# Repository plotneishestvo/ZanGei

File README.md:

# ZanGei — 8HP analog BBD delay

ZanGei is a compact DIY Eurorack bucket-brigade delay, inspired by the [Erica Synths EDU BBD project](https://www.ericasynths.lv/shop/diy-kits-1/edu-diy-bbd/). Two stacked PCBs make room for two different delay chips, shared clocking and a feedback path with its own character. The goal is **character over fidelity**.

The name is a poetic nod to **残心 (*zanshin*)** in iaido and other martial arts: awareness that remains after an action. It carries that idea into sound as **残韻**—“lingering resonance,” like a bell still ringing after the strike, or an echo carrying something of the past. **ZanGei** is a coined project name, not a standard Japanese reading of those kanji.

**Prototype, not a finished kit:** the complete module has not yet been assembled, calibrated or hardware-qualified. Delay/flanger/chorus behaviour is the design intent, not a measured performance specification.

## What it does

- Mono analog audio path using **V3208D (2048 stages)** and **V3205SD (4096 stages)**.
- Parallel/series input routing for the second BBD, with a blend between the two delay branches.
- Shared CD4046 clock with TC4428AEPA driver, TIME CV and INHIBIT CV.
- Feedback CHARACTER combines pre-filtering and drive; AMOUNT controls the return level.
- Independent dry tap, final DRY/WET blend and SOFT/OFF/DARK wet-output filtering.
- **8HP / 3U**, with two **37.5 × 110 mm** PCBs; requires **±12 V and bus +5 V** through a 16-pin cable.

## Signal path

```mermaid
flowchart LR
    IN["Audio input buffer"] --> DRY["Fixed dry tap"]
    IN --> INPUT["INPUT level"]
    INPUT --> SUM["Input and feedback summer"]
    SUM --> B1["V3208D and reconstruction"]
    SUM --> ROUTE["Parallel / series source"]
    B1 --> ROUTE
    ROUTE --> B2["V3205SD and reconstruction"]
    B1 --> BLEND["Tap blend"]
    B2 --> BLEND
    BLEND --> SH["Shared sample-and-hold"]
    SH --> WET["Wet recovery and output filter"]
    WET --> MIX["DRY/WET and output buffer"]
    DRY --> MIX
    MIX --> OUT["Audio output"]
    SH --> CHAR["CHARACTER filter and drive"]
    CHAR --> AMOUNT["AMOUNT and return amplifier"]
    AMOUNT --> SUM
```

## Open and explore

Open **[`schematics/BBD_Buffer.kicad_pro`](schematics/BBD_Buffer.kicad_pro)** in **KiCad 10**. Its root schematic links seven electrical sheets; the PCB contains CORE and CONTROL side by side for editing, not one wide finished board. Project-local symbols, footprints and component models are included; KiCad's standard libraries are also required.

- [Architecture and controls](docs/ARCHITECTURE.md)
- [Prototype build, power, stack and fabrication notes](docs/BUILD.md)
- [One-module BOM](bom/v0.1/BOM.md), [grouped CSV](bom/v0.1/BOM_GROUPED.csv) and [per-reference CSV](bom/v0.1/BOM_PER_REFERENCE.csv)
- [Assembly access and sequencing](schematics/assembly/README.md) and [routing limitations](schematics/routing/README.md)
- [Panel source and printable fit prototype](mechanical/README.md)
- [Component datasheets](docs/datasheets/README.md)

The native KiCad files define the implemented circuit. Documentation and 3D envelopes do not certify physical fit or safe operation. Existing assembly/silkscreen findings, clock timing, power bring-up and complete-module performance remain prototype checks. Do not connect an unverified assembly directly to a valuable rack.

## Repository

| Directory       | Purpose                                                                  |
| --------------- | ------------------------------------------------------------------------ |
| `schematics/`   | Main KiCad design, custom libraries, component models and review records |
| `docs/`         | Self-contained architecture, build notes and datasheets                  |
| `bom/v0.1/`     | One-module parts and additional assembly hardware                        |
| `mechanical/`   | Editable panel source and panel exports                                  |
| `simulation/`   | Retained circuit studies; not complete-module validation                 |
| `test_signals/` | Audio used for listening experiments                                     |

The BOM covers 157 schematic positions plus separate sockets and hardware. Generated manufacturing files and full-board FreeCAD review assemblies are local working artifacts, not a fabrication release. See the [simulation guide](simulation/README.md) for the historical scope and requirements of the retained studies.

### PCB render:

## Licence and attribution

Project-authored schematics, PCB layouts, mechanical designs, scripts and documentation are [MIT-licensed](LICENSE), including permission to manufacture and sell hardware from the project-authored designs. See [licensing scope and third-party exceptions](docs/LICENSING.md). Third-party datasheets, library assets and simulation models retain their own notices and terms. This is an independent, AI-assisted DIY project, not an official Erica Synths, Coolaudio or other manufacturer's product.

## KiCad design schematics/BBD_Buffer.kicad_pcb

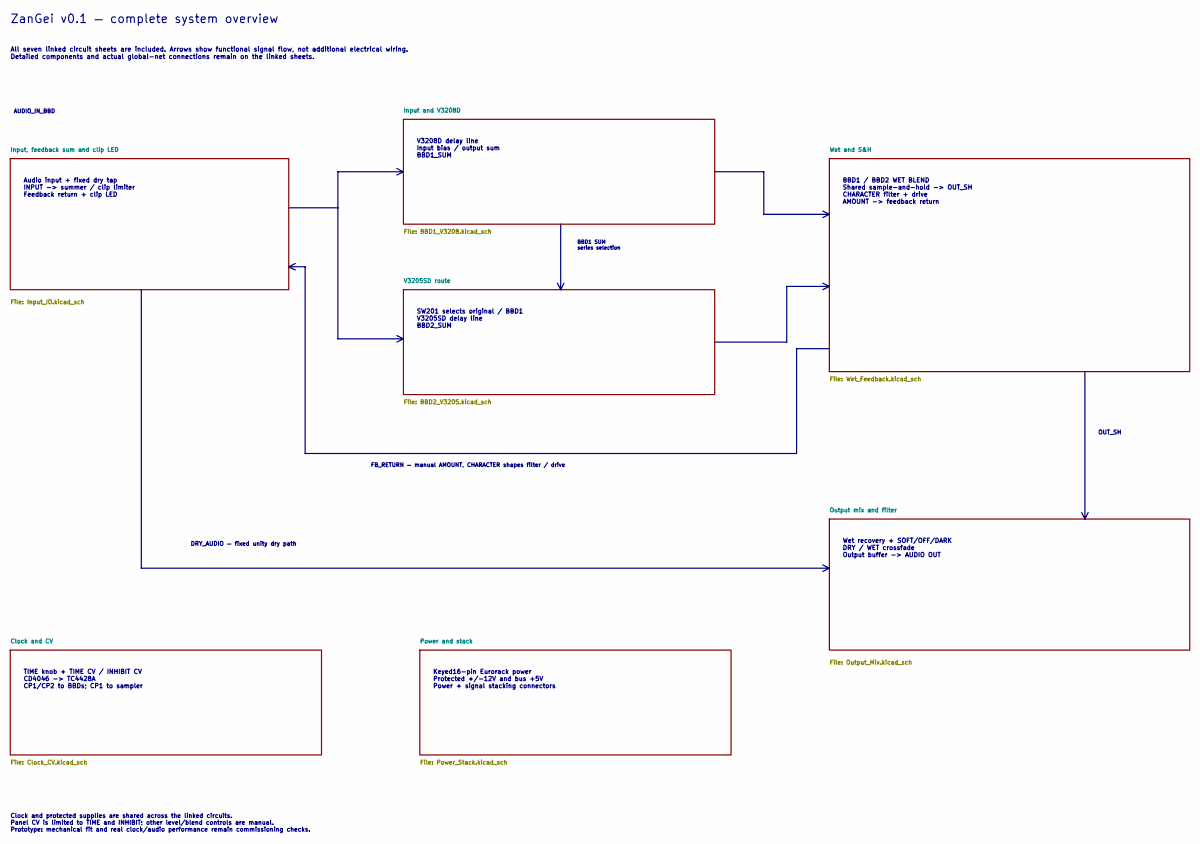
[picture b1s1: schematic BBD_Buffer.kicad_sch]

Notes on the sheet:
V3208D delay line Input bias / output sum BBD1_SUM
Wet recovery + SOFT/OFF/DARK DRY / WET crossfade Output buffer -> AUDIO OUT
BBD1 / BBD2 WET BLEND Shared sample-and-hold -> OUT_SH CHARACTER filter + drive AMOUNT -> feedback return
Audio input + fixed dry tap INPUT -> summer / clip limiter Feedback return + clip LED
TIME knob + TIME CV / INHIBIT CV CD4046 -> TC4428A CP1/CP2 to BBDs; CP1 to sampler
Keyed16-pin Eurorack power Protected +/-12V and bus +5V Power + signal stacking connectors
SW201 selects original / BBD1 V3205SD delay line BBD2_SUM
ZanGei v0.1 — complete system overview
All seven linked circuit sheets are included. Arrows show functional signal flow, not additional electrical wiring. Detailed components and actual global-net connections remain on the linked sheets.
AUDIO_IN_BBD
BBD1 SUM series selection
FB_RETURN — manual AMOUNT, CHARACTER shapes filter / drive
DRY_AUDIO — fixed unity dry path
OUT_SH
Clock and protected supplies are shared across the linked circuits. Panel CV is limited to TIME and INHIBIT; other level/blend controls are manual. Prototype: mechanical fit and real clock/audio performance remain commissioning checks.

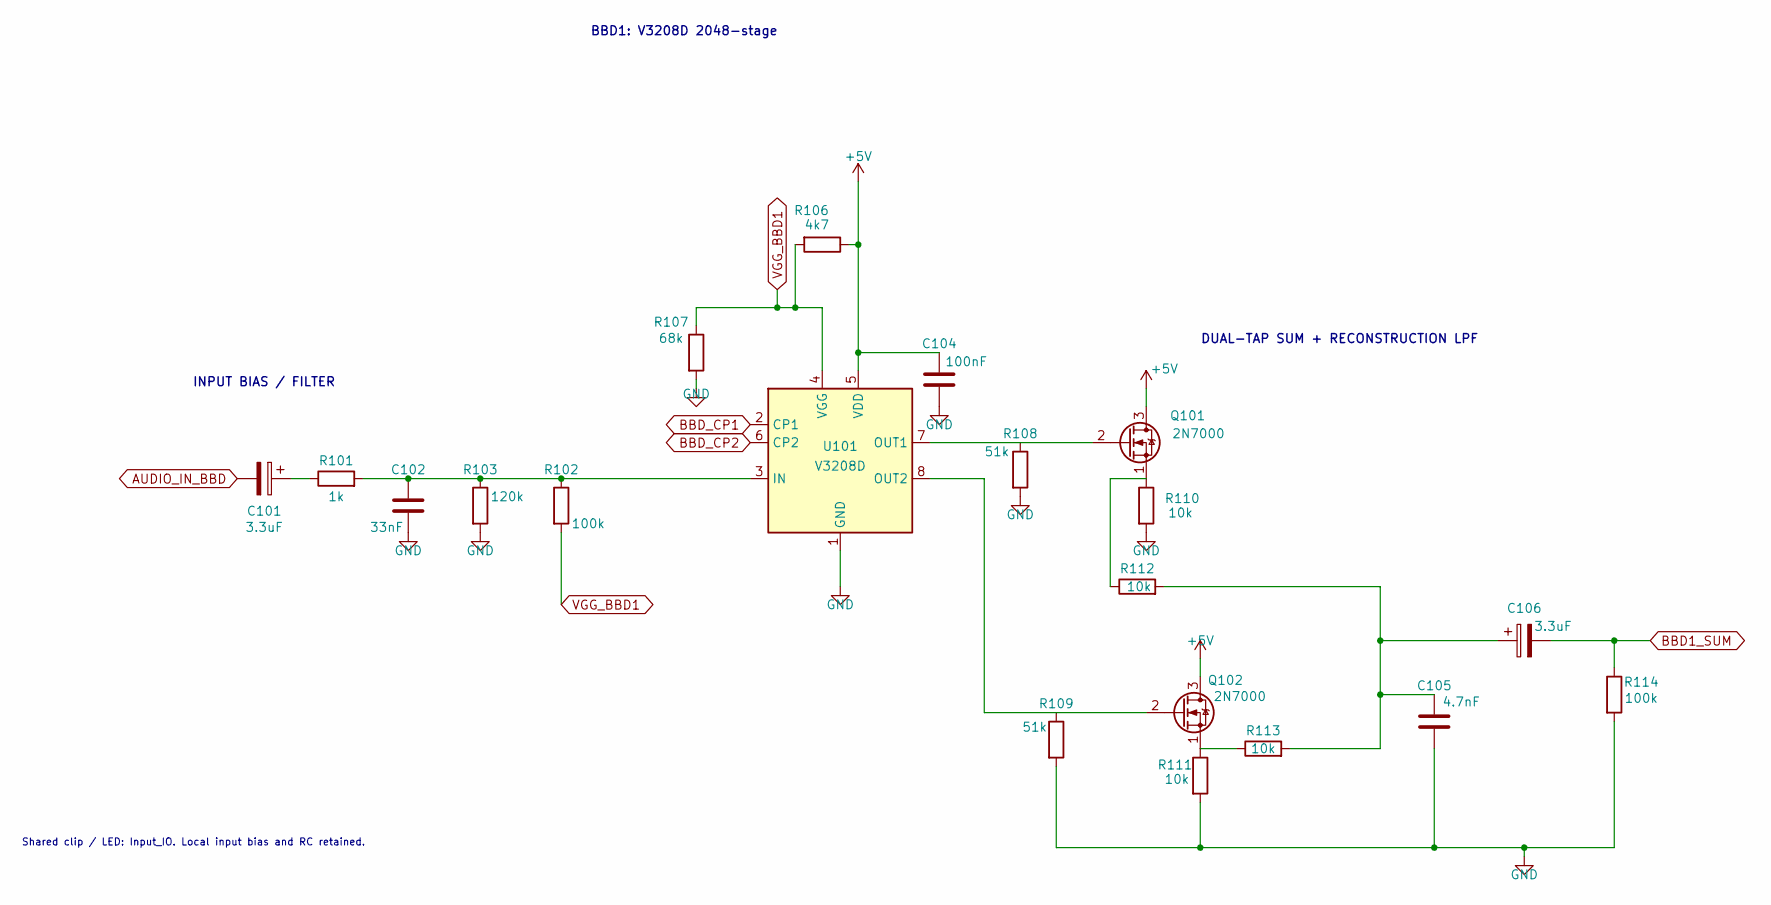
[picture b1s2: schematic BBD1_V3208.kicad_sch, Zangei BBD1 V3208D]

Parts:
C101, C106: 3.3uF; CP_Radial_D5.0mm_P2.50mm
C102: 33nF; C_Rect_L7.2mm_W2.5mm_P5.00mm
C104: 100nF; C_KEMET_C315C104_P2.54_L3.81_W2.54; MPN C315C104K5R5TA
C105: 4.7nF; C_Rect_L7.2mm_W2.5mm_P5.00mm
Q101, Q102: 2N7000; TO-92_Inline
R101: 1k; R_Axial_L6.8mm_D2.5mm_P10.16mm
R102, R114: 100k; R_Axial_L6.8mm_D2.5mm_P10.16mm
R103: 120k; R_Axial_L6.8mm_D2.5mm_P10.16mm
R106: 4k7; R_Axial_L6.8mm_D2.5mm_P10.16mm
R107: 68k; R_Axial_L6.8mm_D2.5mm_P10.16mm
R108, R109: 51k; R_Axial_L6.8mm_D2.5mm_P10.16mm
R110, R111, R112, R113: 10k; R_Axial_L6.8mm_D2.5mm_P10.16mm
U101: V3208D; DIP-8_W7.62mm_Socket

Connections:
+5V: C104.1, Q101.3 (D), Q102.3 (D), R106.1, U101.5 (VDD); also elsewhere on the board
AUDIO_IN_BBD: C101.2; also elsewhere on the board
BBD1_SUM: C106.2, R114.1; also elsewhere on the board
BBD_CP1: U101.2 (CP1); also elsewhere on the board
BBD_CP2: U101.6 (CP2); also elsewhere on the board
GND: C102.2, C104.2, C105.2, R103.2, R107.2, R108.2, R109.2, R110.2, R111.2, R114.2, U101.1 (GND); also elsewhere on the board
unnamed: C101.1, R101.1
unnamed: C105.1, C106.1, R112.2, R113.2
unnamed: Q101.2 (G), R108.1, U101.7 (OUT1)
unnamed: Q101.1 (S), R110.1, R112.1
unnamed: Q102.2 (G), R109.1, U101.8 (OUT2)
unnamed: Q102.1 (S), R111.1, R113.1
unnamed: C102.1, R101.2, R102.1, R103.1, U101.3 (IN)
VGG_BBD1: R102.2, R106.2, R107.1, U101.4 (VGG)

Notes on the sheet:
INPUT BIAS / FILTER
Shared clip / LED: Input_IO. Local input bias and RC retained.
BBD1: V3208D 2048-stage
DUAL-TAP SUM + RECONSTRUCTION LPF

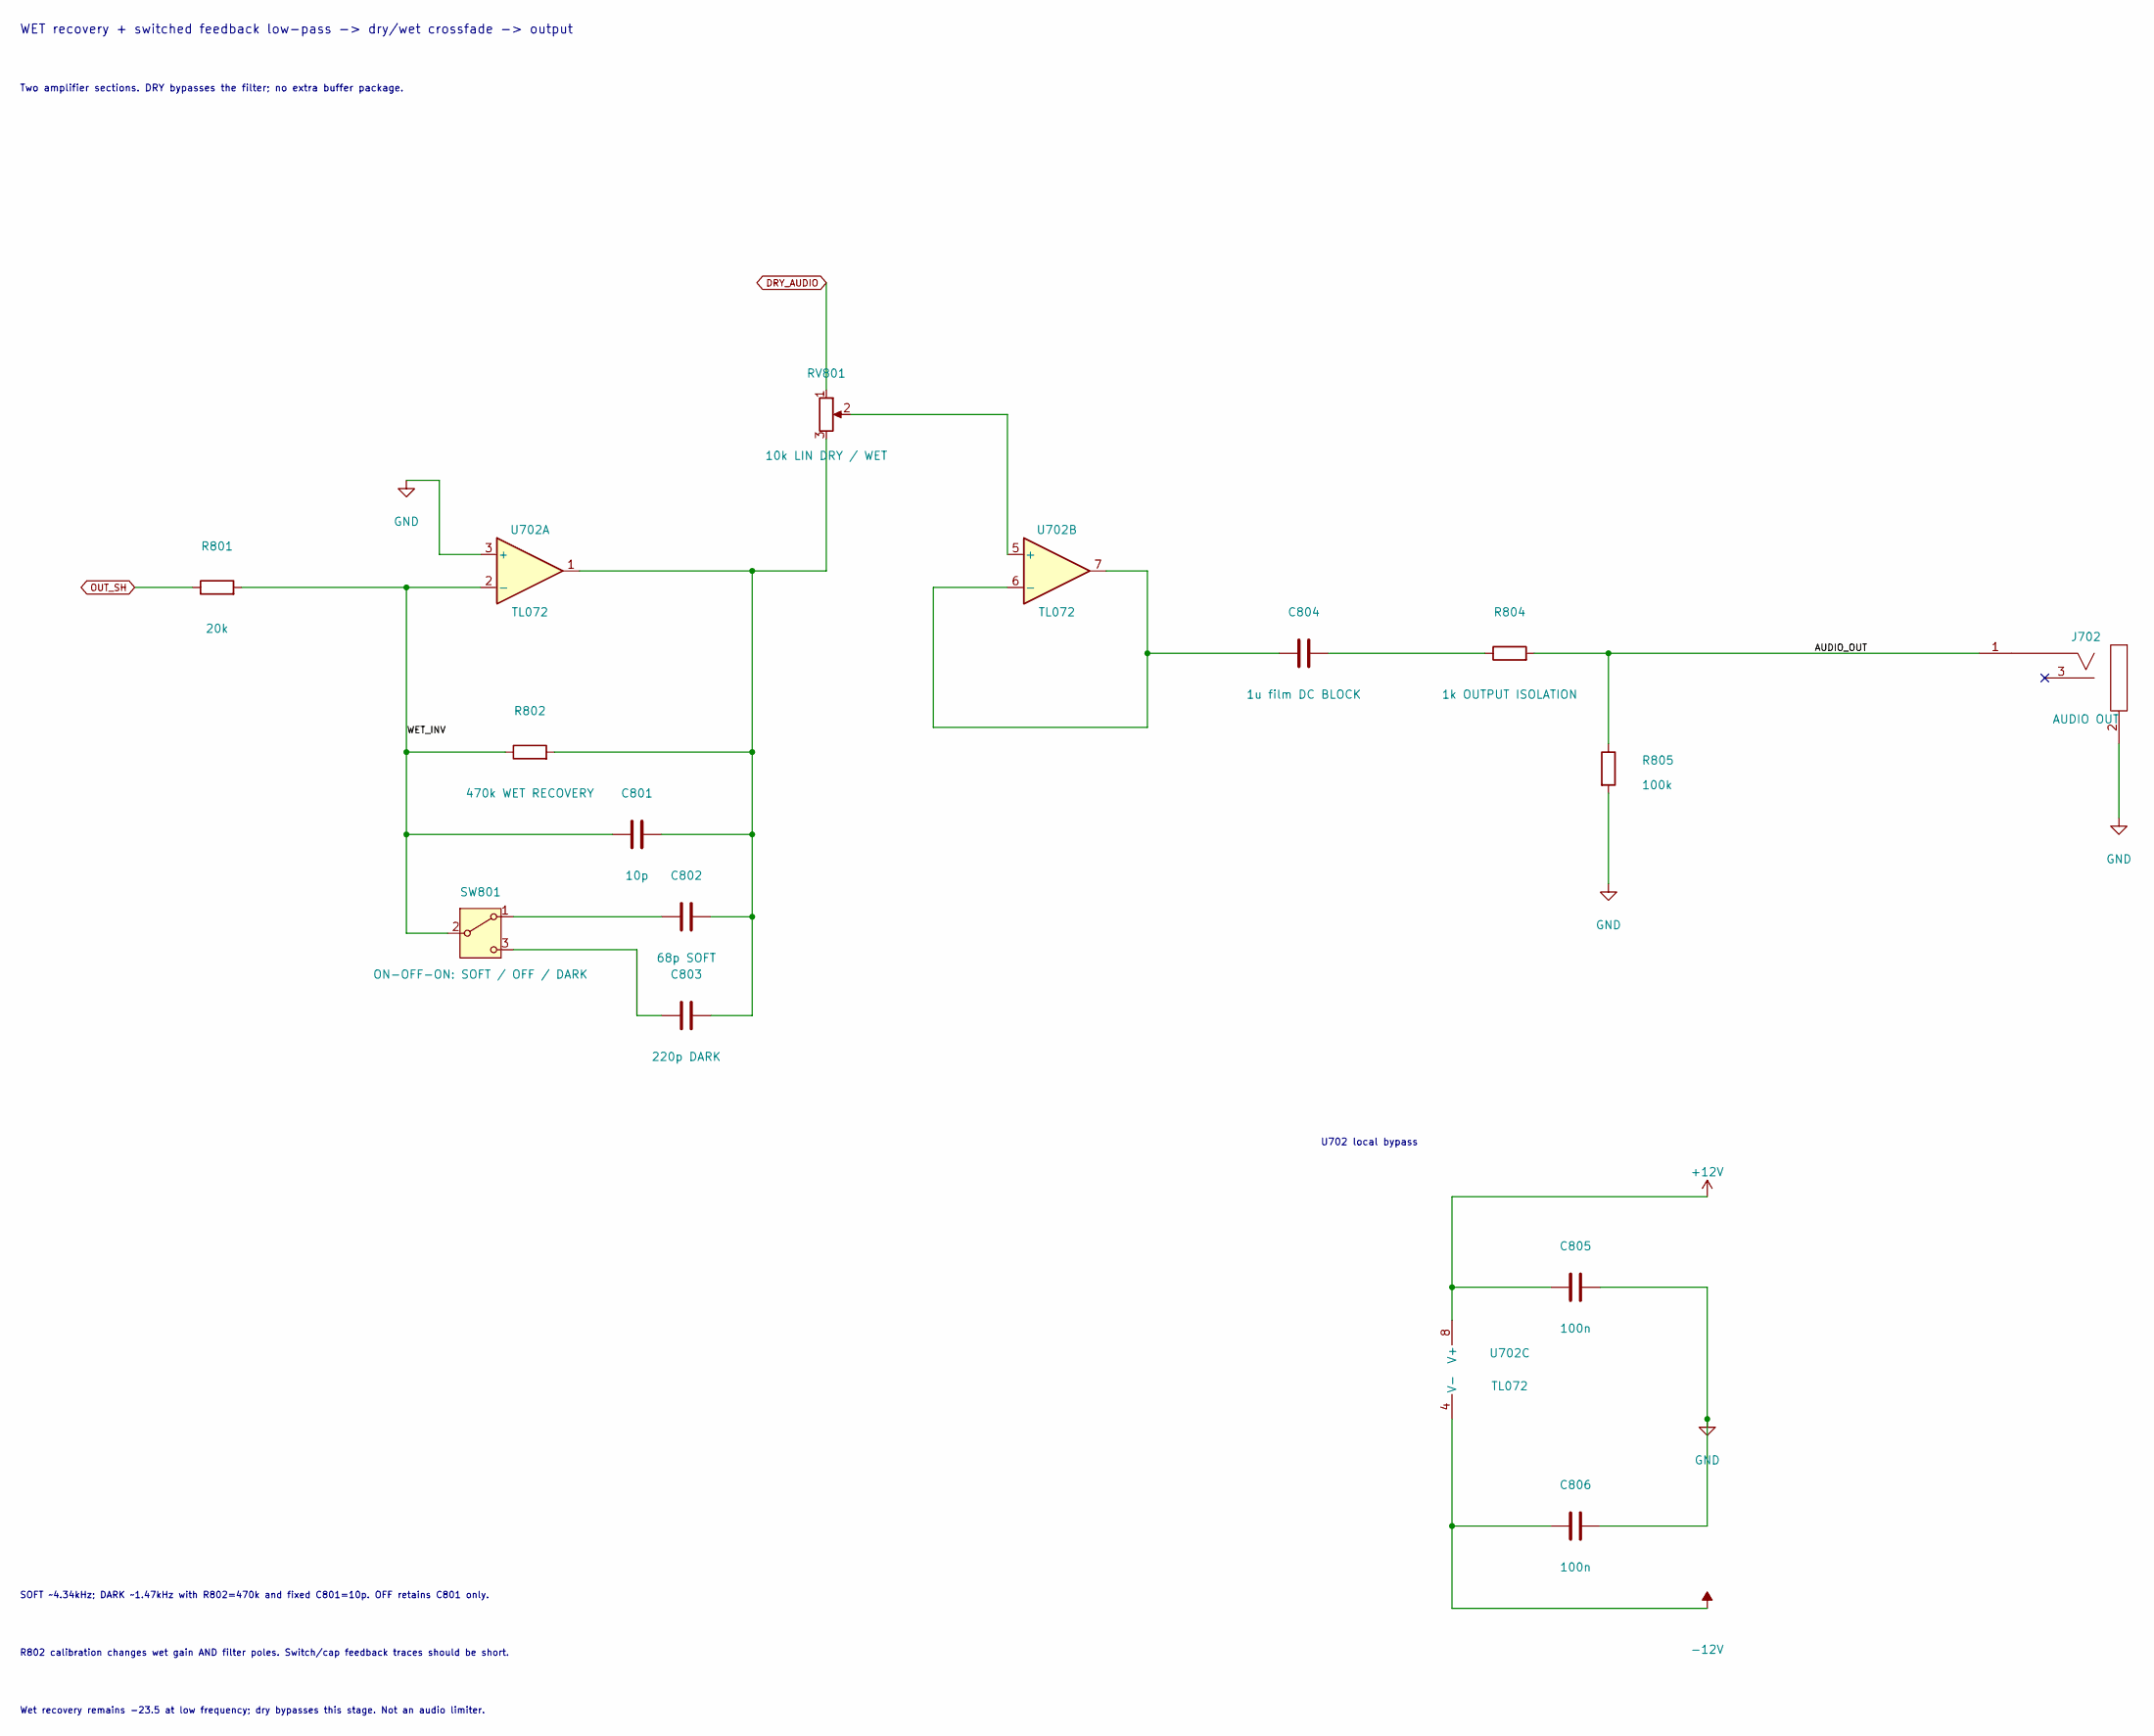
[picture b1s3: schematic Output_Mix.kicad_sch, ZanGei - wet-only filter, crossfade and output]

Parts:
C801: 10p; C_Radial_KEMET_C315_P2.54_Body3.81x5.0
C802: 68p SOFT; C_Radial_KEMET_C315_P2.54_Body3.81x5.0
C803: 220p DARK; C_Radial_KEMET_C315_P2.54_Body3.81x5.0
C804: 1u film DC BLOCK; C_Rect_L7.2mm_W6.0mm_P5.00mm
C805, C806: 100n; C_KEMET_C315C104_P2.54_L3.81_W2.54; MPN C315C104K5R5TA
J702: AUDIO OUT; Jack_WQP518MA_PJ398SM_Numeric
R801: 20k; R_Axial_L6.8mm_D2.5mm_P10.16mm
R802: 470k WET RECOVERY; R_Axial_L6.8mm_D2.5mm_P10.16mm
R804: 1k OUTPUT ISOLATION; R_Axial_L6.8mm_D2.5mm_P10.16mm
R805: 100k; R_Axial_L6.8mm_D2.5mm_P10.16mm
RV801: 10k LIN DRY / WET; Potentiometer_RV09_ExplodingShed_101018
SW801: ON-OFF-ON: SOFT / OFF / DARK; Switch_Salecom_SKS_SP_Straight
U702: TL072; DIP-8_W7.62mm_Socket

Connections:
+12V: C805.1, U702.8 (V+); also elsewhere on the board
-12V: C806.1, U702.4 (V-); also elsewhere on the board
/Output mix and filter/AUDIO_OUT: J702.1 (SIG), R804.2, R805.1
/Output mix and filter/WET_INV: C801.1, R801.2, R802.1, SW801.2 (B), U702.2 (-)
DRY_AUDIO: RV801.1; also elsewhere on the board
GND: C805.2, C806.2, J702.2 (SHEILD), R805.2, U702.3 (+); also elsewhere on the board
unnamed: C801.2, C802.2, C803.2, R802.2, RV801.3, U702.1
unnamed: C804.2, R804.1
unnamed: C802.1, SW801.1 (A)
unnamed: C803.1, SW801.3 (C)
unnamed: RV801.2, U702.5 (+)
unnamed: C804.1, U702.6 (-), U702.7
OUT_SH: R801.1; also elsewhere on the board

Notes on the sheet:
R802 calibration changes wet gain AND filter poles. Switch/cap feedback traces should be short.
U702 local bypass
Two amplifier sections. DRY bypasses the filter; no extra buffer package.
SOFT ~4.34kHz; DARK ~1.47kHz with R802=470k and fixed C801=10p. OFF retains C801 only.
WET recovery + switched feedback low-pass -> dry/wet crossfade -> output
Wet recovery remains -23.5 at low frequency; dry bypasses this stage. Not an audio limiter.

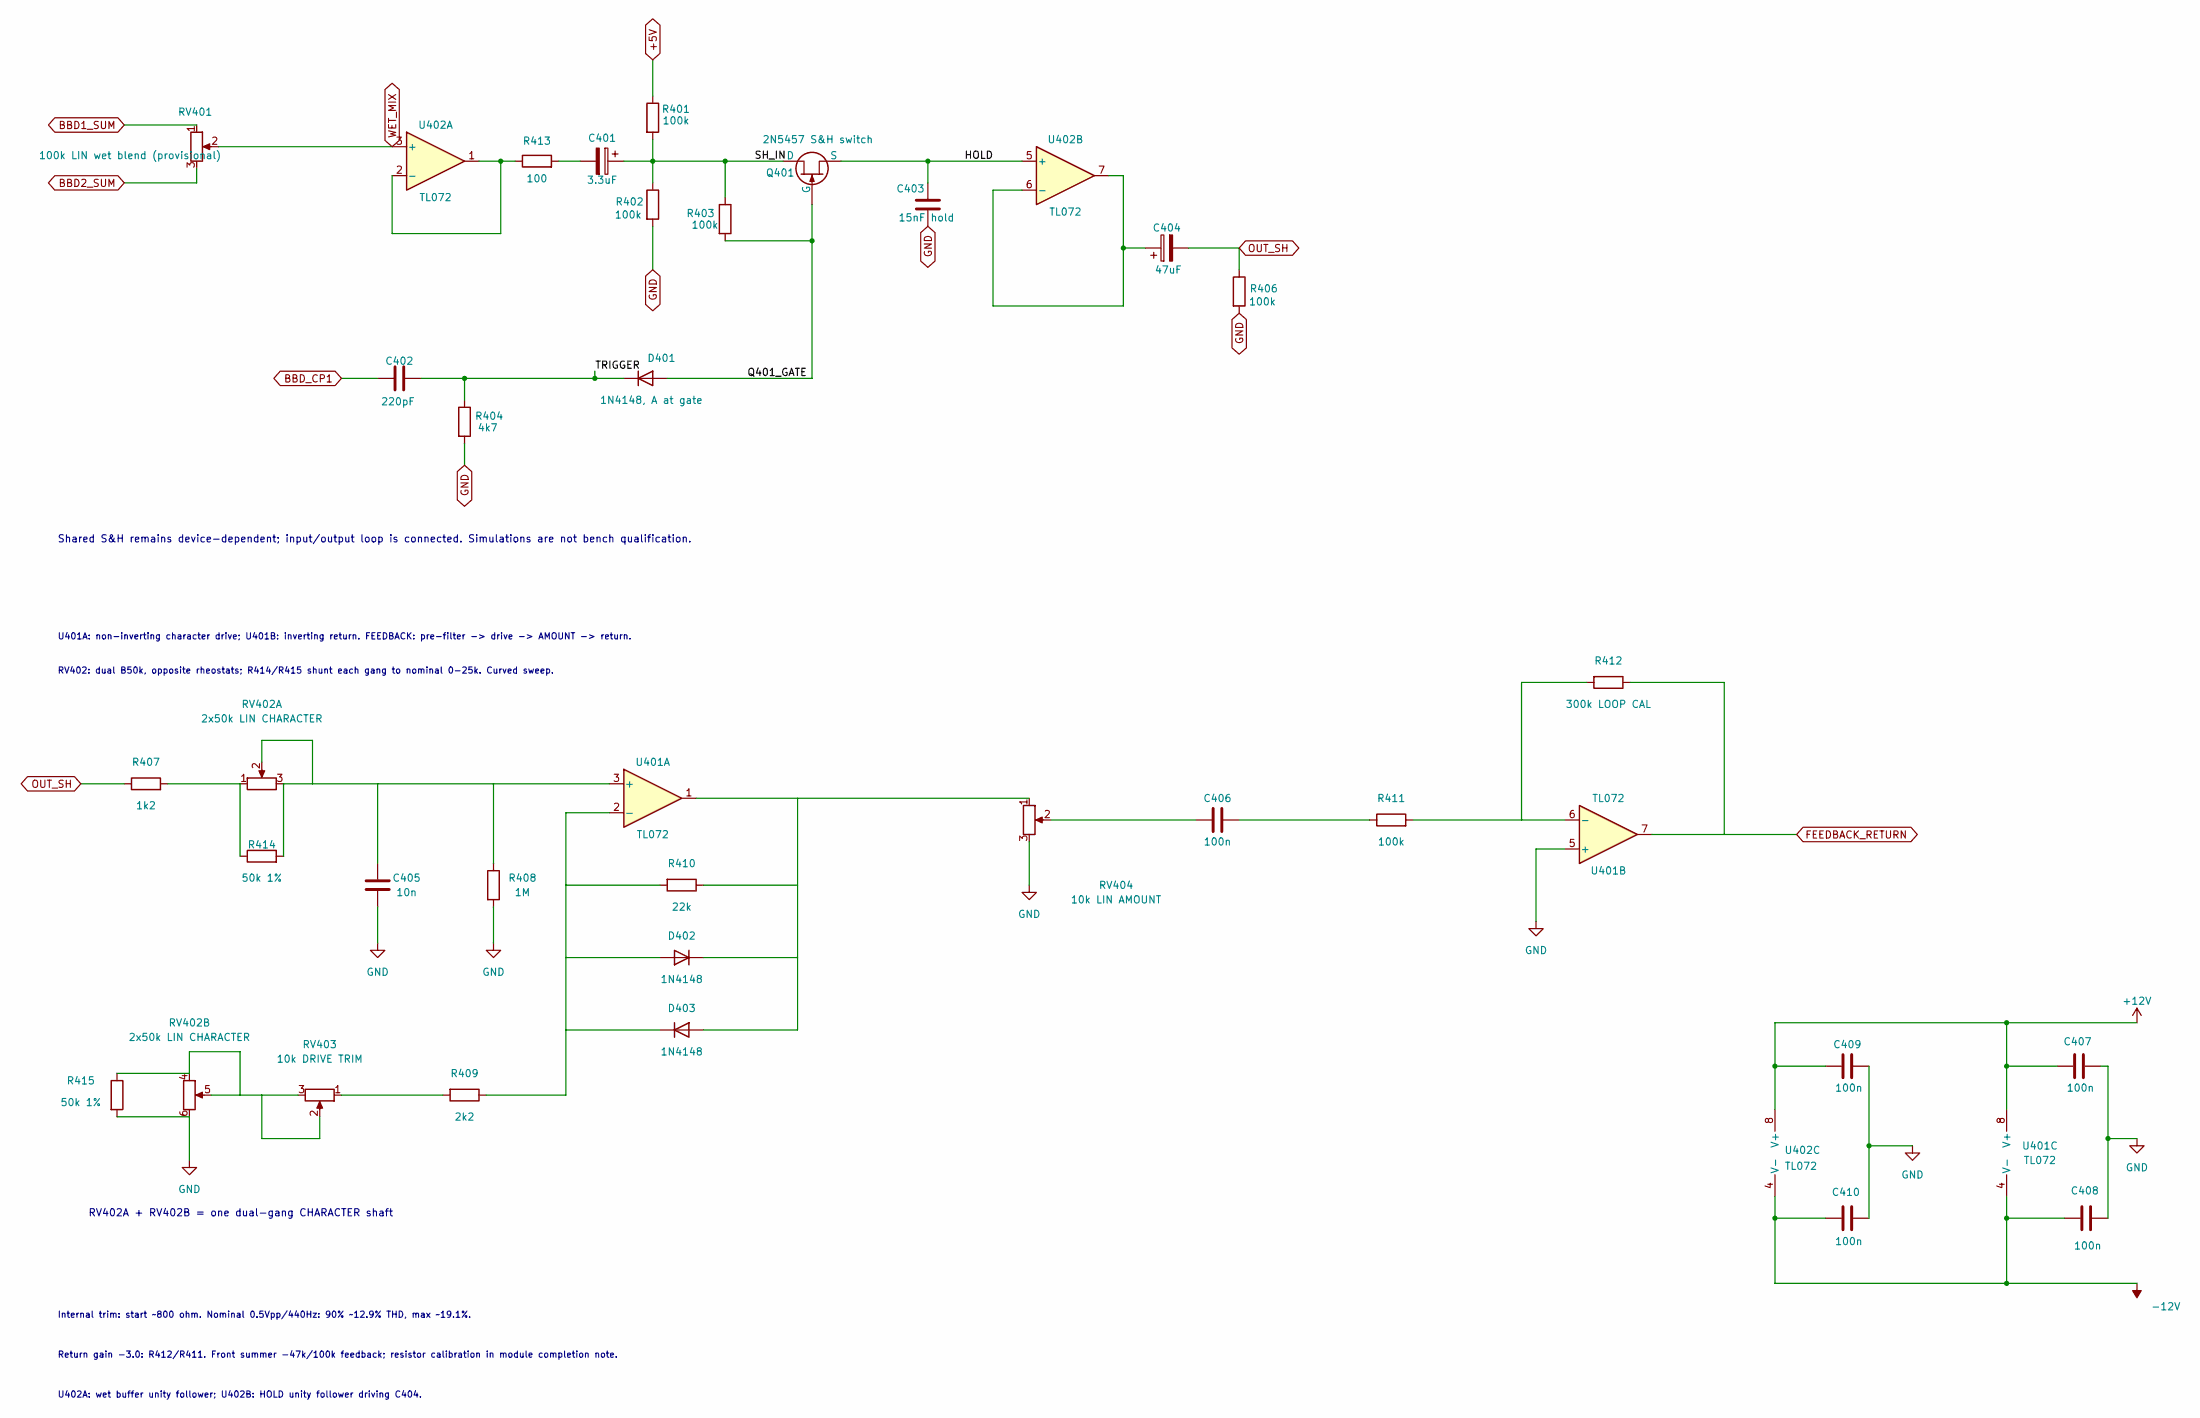
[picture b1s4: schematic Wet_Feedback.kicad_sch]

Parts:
C401: 3.3uF; CP_Radial_D5.0mm_P2.50mm
C402: 220pF; C_Radial_KEMET_C315_P2.54_Body3.81x5.0
C403: 15nF hold; C_Rect_L7.2mm_W4.5mm_P5.00mm
C404: 47uF; CP_Radial_D6.3mm_P2.50mm
C405: 10n; C_Rect_L7.2mm_W2.5mm_P5.00mm
C406, C407, C408, C409, C410: 100n; C_KEMET_C315C104_P2.54_L3.81_W2.54; MPN C315C104K5R5TA
D401: 1N4148, A at gate; D_DO-35_SOD27_P7.62mm_Horizontal
D402, D403: 1N4148; D_DO-35_SOD27_P7.62mm_Horizontal
Q401: 2N5457 S&H switch; TO-92_Inline
R401, R402, R403, R406, R411: 100k; R_Axial_L6.8mm_D2.5mm_P10.16mm
R404: 4k7; R_Axial_L6.8mm_D2.5mm_P10.16mm
R407: 1k2; R_Axial_L6.8mm_D2.5mm_P10.16mm
R408: 1M; R_Axial_L6.8mm_D2.5mm_P10.16mm
R409: 2k2; R_Axial_L6.8mm_D2.5mm_P10.16mm
R410: 22k; R_Axial_L6.8mm_D2.5mm_P10.16mm
R412: 300k LOOP CAL; R_Axial_L6.8mm_D2.5mm_P10.16mm
R413: 100; R_Axial_L6.8mm_D2.5mm_P10.16mm
R414, R415: 50k 1%; R_Axial_L6.8mm_D2.5mm_P10.16mm
RV401: 100k LIN wet blend (provisional); Potentiometer_RV09_ExplodingShed_101018
RV402: 2x50k LIN CHARACTER; Potentiometer_Alpha_RD902F-40-00D_Dual_Vertical
RV403: 10k DRIVE TRIM; Trimmer_Nidec_CT-6EP
RV404: 10k LIN AMOUNT; Potentiometer_RV09_ExplodingShed_101018
U401, U402: TL072; DIP-8_W7.62mm_Socket

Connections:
+5V: R401.1; also elsewhere on the board
+12V: C407.1, C409.1, U401.8 (V+), U402.8 (V+); also elsewhere on the board
-12V: C408.1, C410.1, U401.4 (V-), U402.4 (V-); also elsewhere on the board
/Wet and S&H/HOLD: C403.1, Q401.2 (S), U402.5 (+)
/Wet and S&H/Q401_GATE: D401.2 (A), Q401.3 (G), R403.2
/Wet and S&H/SH_IN: C401.1, Q401.1 (D), R401.2, R402.1, R403.1
/Wet and S&H/TRIGGER: C402.2, D401.1 (K), R404.1
BBD1_SUM: RV401.1; also elsewhere on the board
BBD2_SUM: RV401.3; also elsewhere on the board
BBD_CP1: C402.1; also elsewhere on the board
FEEDBACK_RETURN: R412.1, U401.7; also elsewhere on the board
GND: C403.2, C405.2, C407.2, C408.2, C409.2, C410.2, R402.2, R404.2, R406.2, R408.2, R415.2, RV402.6, RV404.3, U401.5 (+); also elsewhere on the board
unnamed: C401.2, R413.2
unnamed: C406.1, RV404.2
unnamed: C406.2, R411.1
unnamed: D402.2 (A), D403.1 (K), R409.1, R410.2, U401.2 (-)
unnamed: D402.1 (K), D403.2 (A), R410.1, RV404.1, U401.1
unnamed: R407.2, R414.1, RV402.1
unnamed: R409.2, RV403.1
unnamed: R415.1, RV402.4, RV402.5, RV403.2, RV403.3
unnamed: C405.1, R408.1, R414.2, RV402.2, RV402.3, U401.3 (+)
unnamed: R411.2, R412.2, U401.6 (-)
unnamed: R413.1, U402.1, U402.2 (-)
unnamed: C404.1, U402.6 (-), U402.7
OUT_SH: C404.2, R406.1, R407.1; also elsewhere on the board
WET_MIX: RV401.2, U402.3 (+); also elsewhere on the board

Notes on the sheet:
Internal trim: start ~800 ohm. Nominal 0.5Vpp/440Hz: 90% ~12.9% THD, max ~19.1%.
U401A: non-inverting character drive; U401B: inverting return. FEEDBACK: pre-filter -> drive -> AMOUNT -> return.
Return gain -3.0: R412/R411. Front summer -47k/100k feedback; resistor calibration in module completion note.
U402A: wet buffer unity follower; U402B: HOLD unity follower driving C404.
RV402A + RV402B = one dual-gang CHARACTER shaft
RV402: dual B50k, opposite rheostats; R414/R415 shunt each gang to nominal 0-25k. Curved sweep.
Shared S&H remains device-dependent; input/output loop is connected. Simulations are not bench qualification.

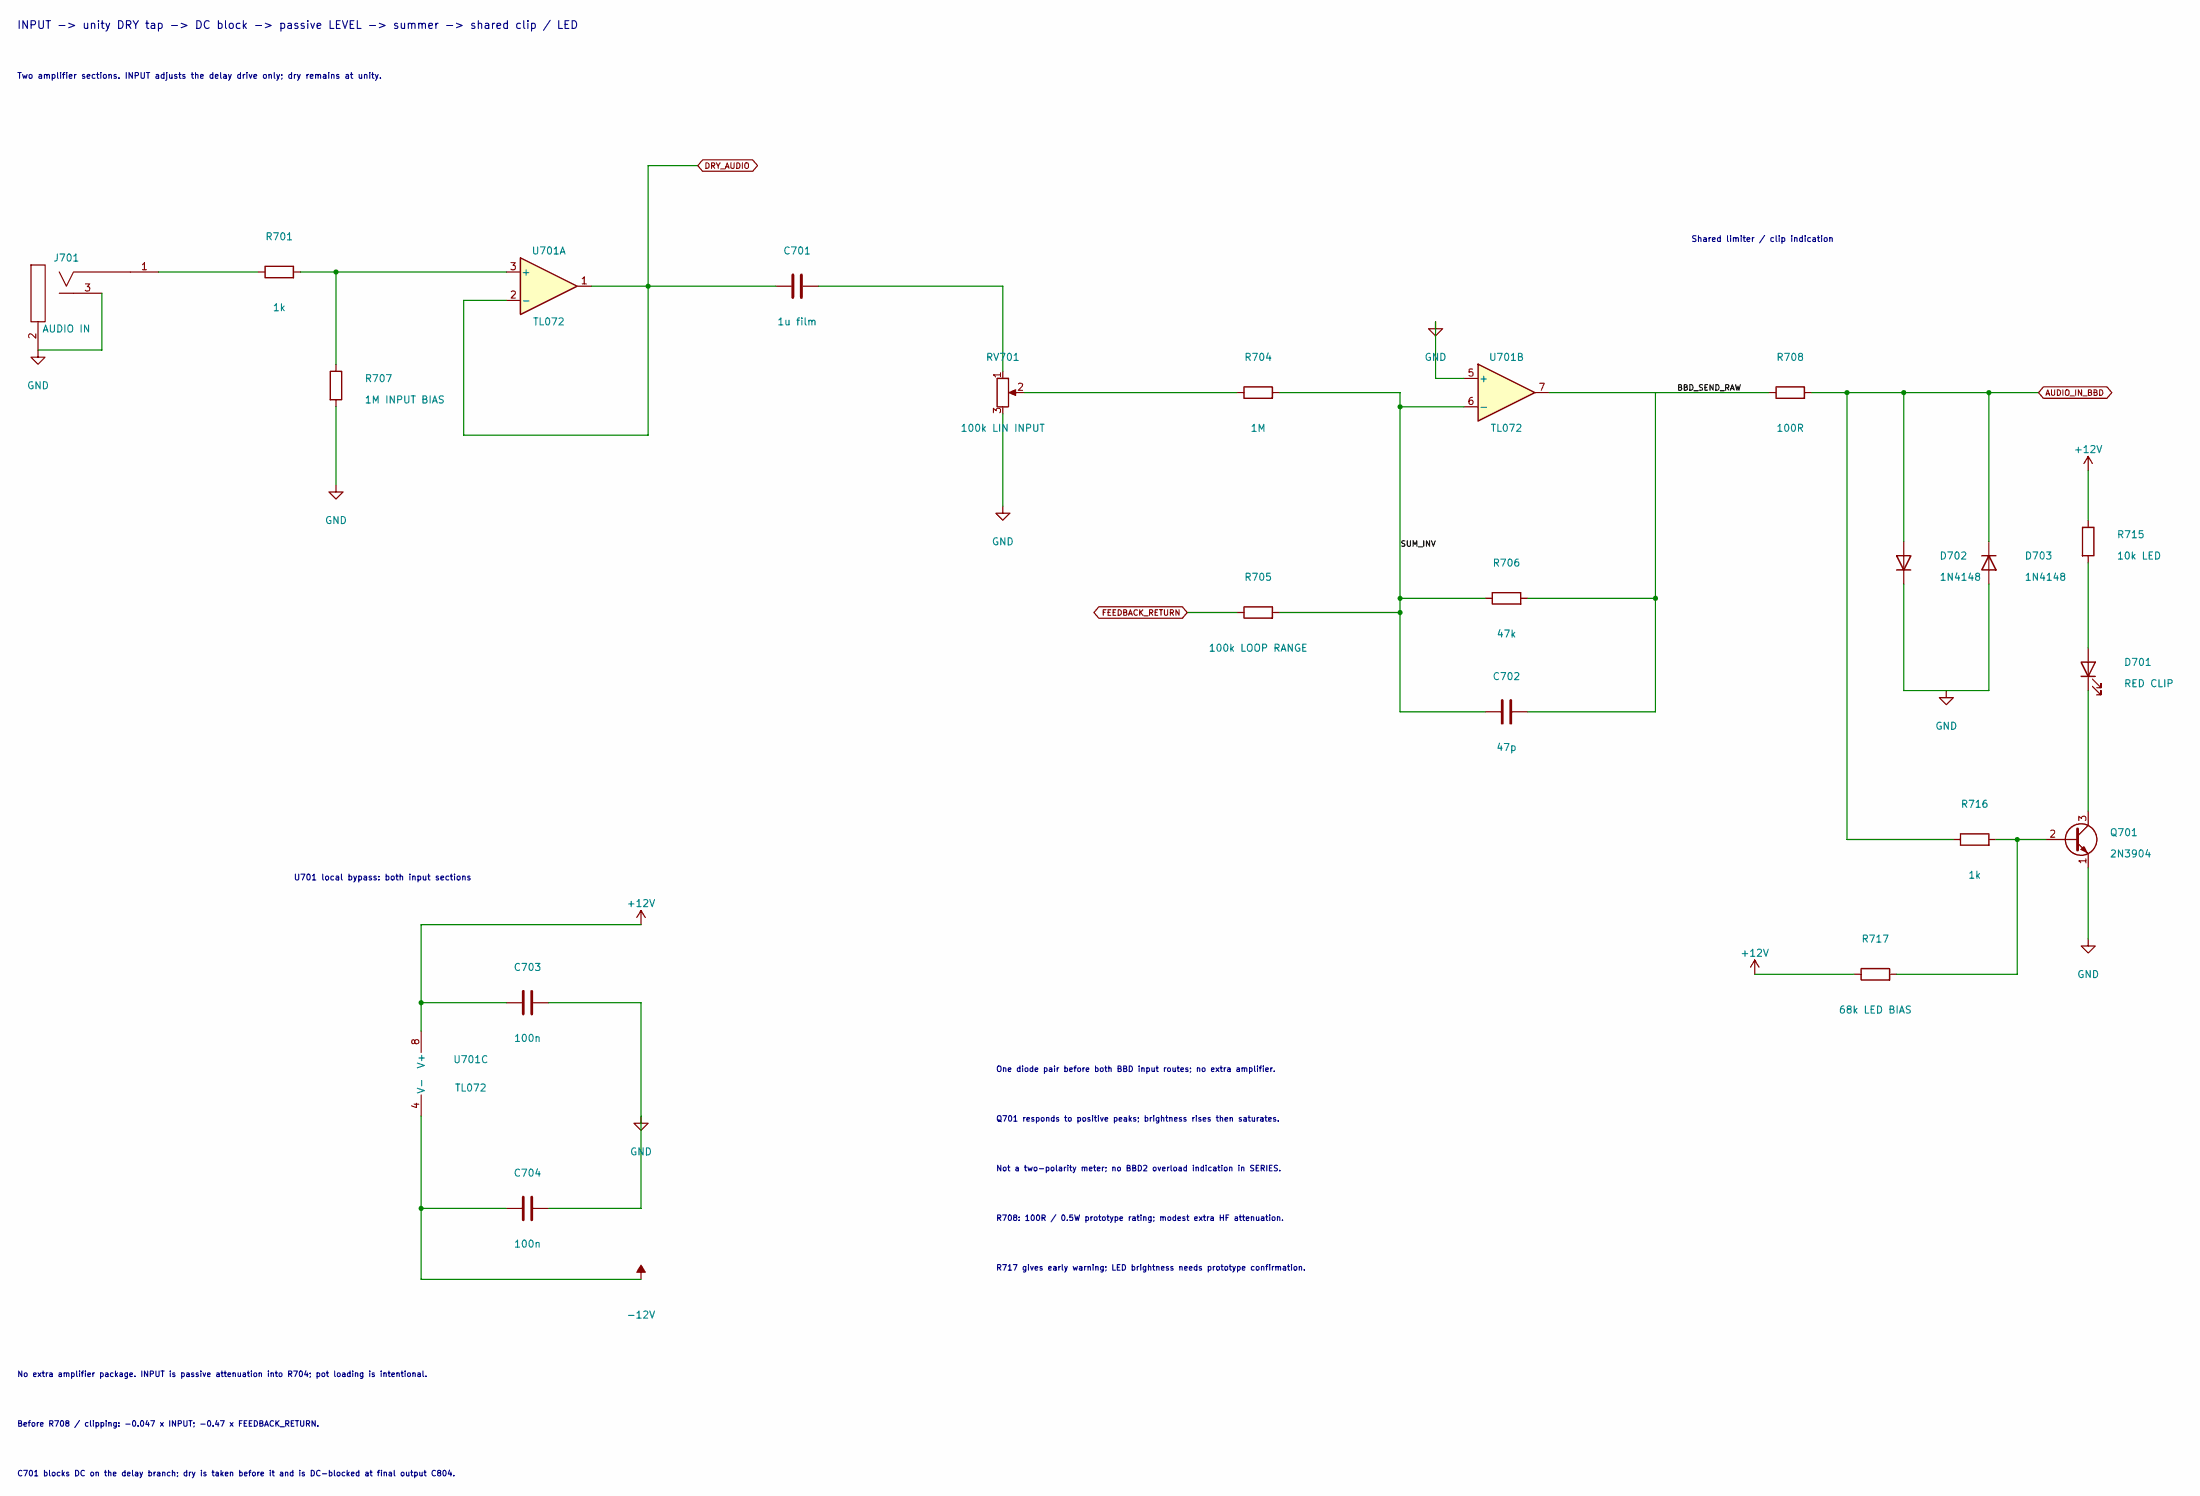
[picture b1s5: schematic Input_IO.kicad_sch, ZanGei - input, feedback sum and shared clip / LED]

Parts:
C701: 1u film; C_Rect_L7.2mm_W6.0mm_P5.00mm
C702: 47p; C_Radial_KEMET_C315_P2.54_Body3.81x5.0
C703, C704: 100n; C_KEMET_C315C104_P2.54_L3.81_W2.54; MPN C315C104K5R5TA
D701: RED CLIP; LED_D3.0mm; MPN WP3A8ID
D702, D703: 1N4148; D_DO-35_SOD27_P7.62mm_Horizontal
J701: AUDIO IN; Jack_WQP518MA_PJ398SM_Numeric
Q701: 2N3904; TO-92_Inline
R701, R716: 1k; R_Axial_L6.8mm_D2.5mm_P10.16mm
R704: 1M; R_Axial_L6.8mm_D2.5mm_P10.16mm
R705: 100k LOOP RANGE; R_Axial_L6.8mm_D2.5mm_P10.16mm
R706: 47k; R_Axial_L6.8mm_D2.5mm_P10.16mm
R707: 1M INPUT BIAS; R_Axial_L6.8mm_D2.5mm_P10.16mm
R708: 100R; R_Axial_L6.8mm_D2.5mm_P10.16mm
R715: 10k LED; R_Axial_L6.8mm_D2.5mm_P10.16mm
R717: 68k LED BIAS; R_Axial_L6.8mm_D2.5mm_P10.16mm
RV701: 100k LIN INPUT; Potentiometer_RV09_ExplodingShed_101018
U701: TL072; DIP-8_W7.62mm_Socket

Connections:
+12V: C703.1, R715.1, R717.1, U701.8 (V+); also elsewhere on the board
-12V: C704.1, U701.4 (V-); also elsewhere on the board
/Input, feedback sum and clip LED/BBD_SEND_RAW: C702.2, R706.2, R708.1, U701.7
/Input, feedback sum and clip LED/SUM_INV: C702.1, R704.2, R705.2, R706.1, U701.6 (-)
AUDIO_IN_BBD: D702.2 (A), D703.1 (K), R708.2, R716.1; also elsewhere on the board
DRY_AUDIO: C701.1, U701.1, U701.2 (-); also elsewhere on the board
FEEDBACK_RETURN: R705.1; also elsewhere on the board
GND: C703.2, C704.2, D702.1 (K), D703.2 (A), J701.2 (SHEILD), J701.3 (SW), Q701.1 (E), R707.2, RV701.3, U701.5 (+); also elsewhere on the board
unnamed: C701.2, RV701.1
unnamed: D701.2 (A), R715.2
unnamed: D701.1 (K), Q701.3 (C)
unnamed: J701.1 (SIG), R701.1
unnamed: Q701.2 (B), R716.2, R717.2
unnamed: R704.1, RV701.2
unnamed: R701.2, R707.1, U701.3 (+)

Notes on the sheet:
One diode pair before both BBD input routes; no extra amplifier.
C701 blocks DC on the delay branch; dry is taken before it and is DC-blocked at final output C804.
R717 gives early warning; LED brightness needs prototype confirmation.
R708: 100R / 0.5W prototype rating; modest extra HF attenuation.
U701 local bypass: both input sections
Before R708 / clipping: -0.047 x INPUT; -0.47 x FEEDBACK_RETURN.
No extra amplifier package. INPUT is passive attenuation into R704; pot loading is intentional.
Shared limiter / clip indication
Q701 responds to positive peaks; brightness rises then saturates.
Not a two-polarity meter; no BBD2 overload indication in SERIES.
INPUT -> unity DRY tap -> DC block -> passive LEVEL -> summer -> shared clip / LED
Two amplifier sections. INPUT adjusts the delay drive only; dry remains at unity.
